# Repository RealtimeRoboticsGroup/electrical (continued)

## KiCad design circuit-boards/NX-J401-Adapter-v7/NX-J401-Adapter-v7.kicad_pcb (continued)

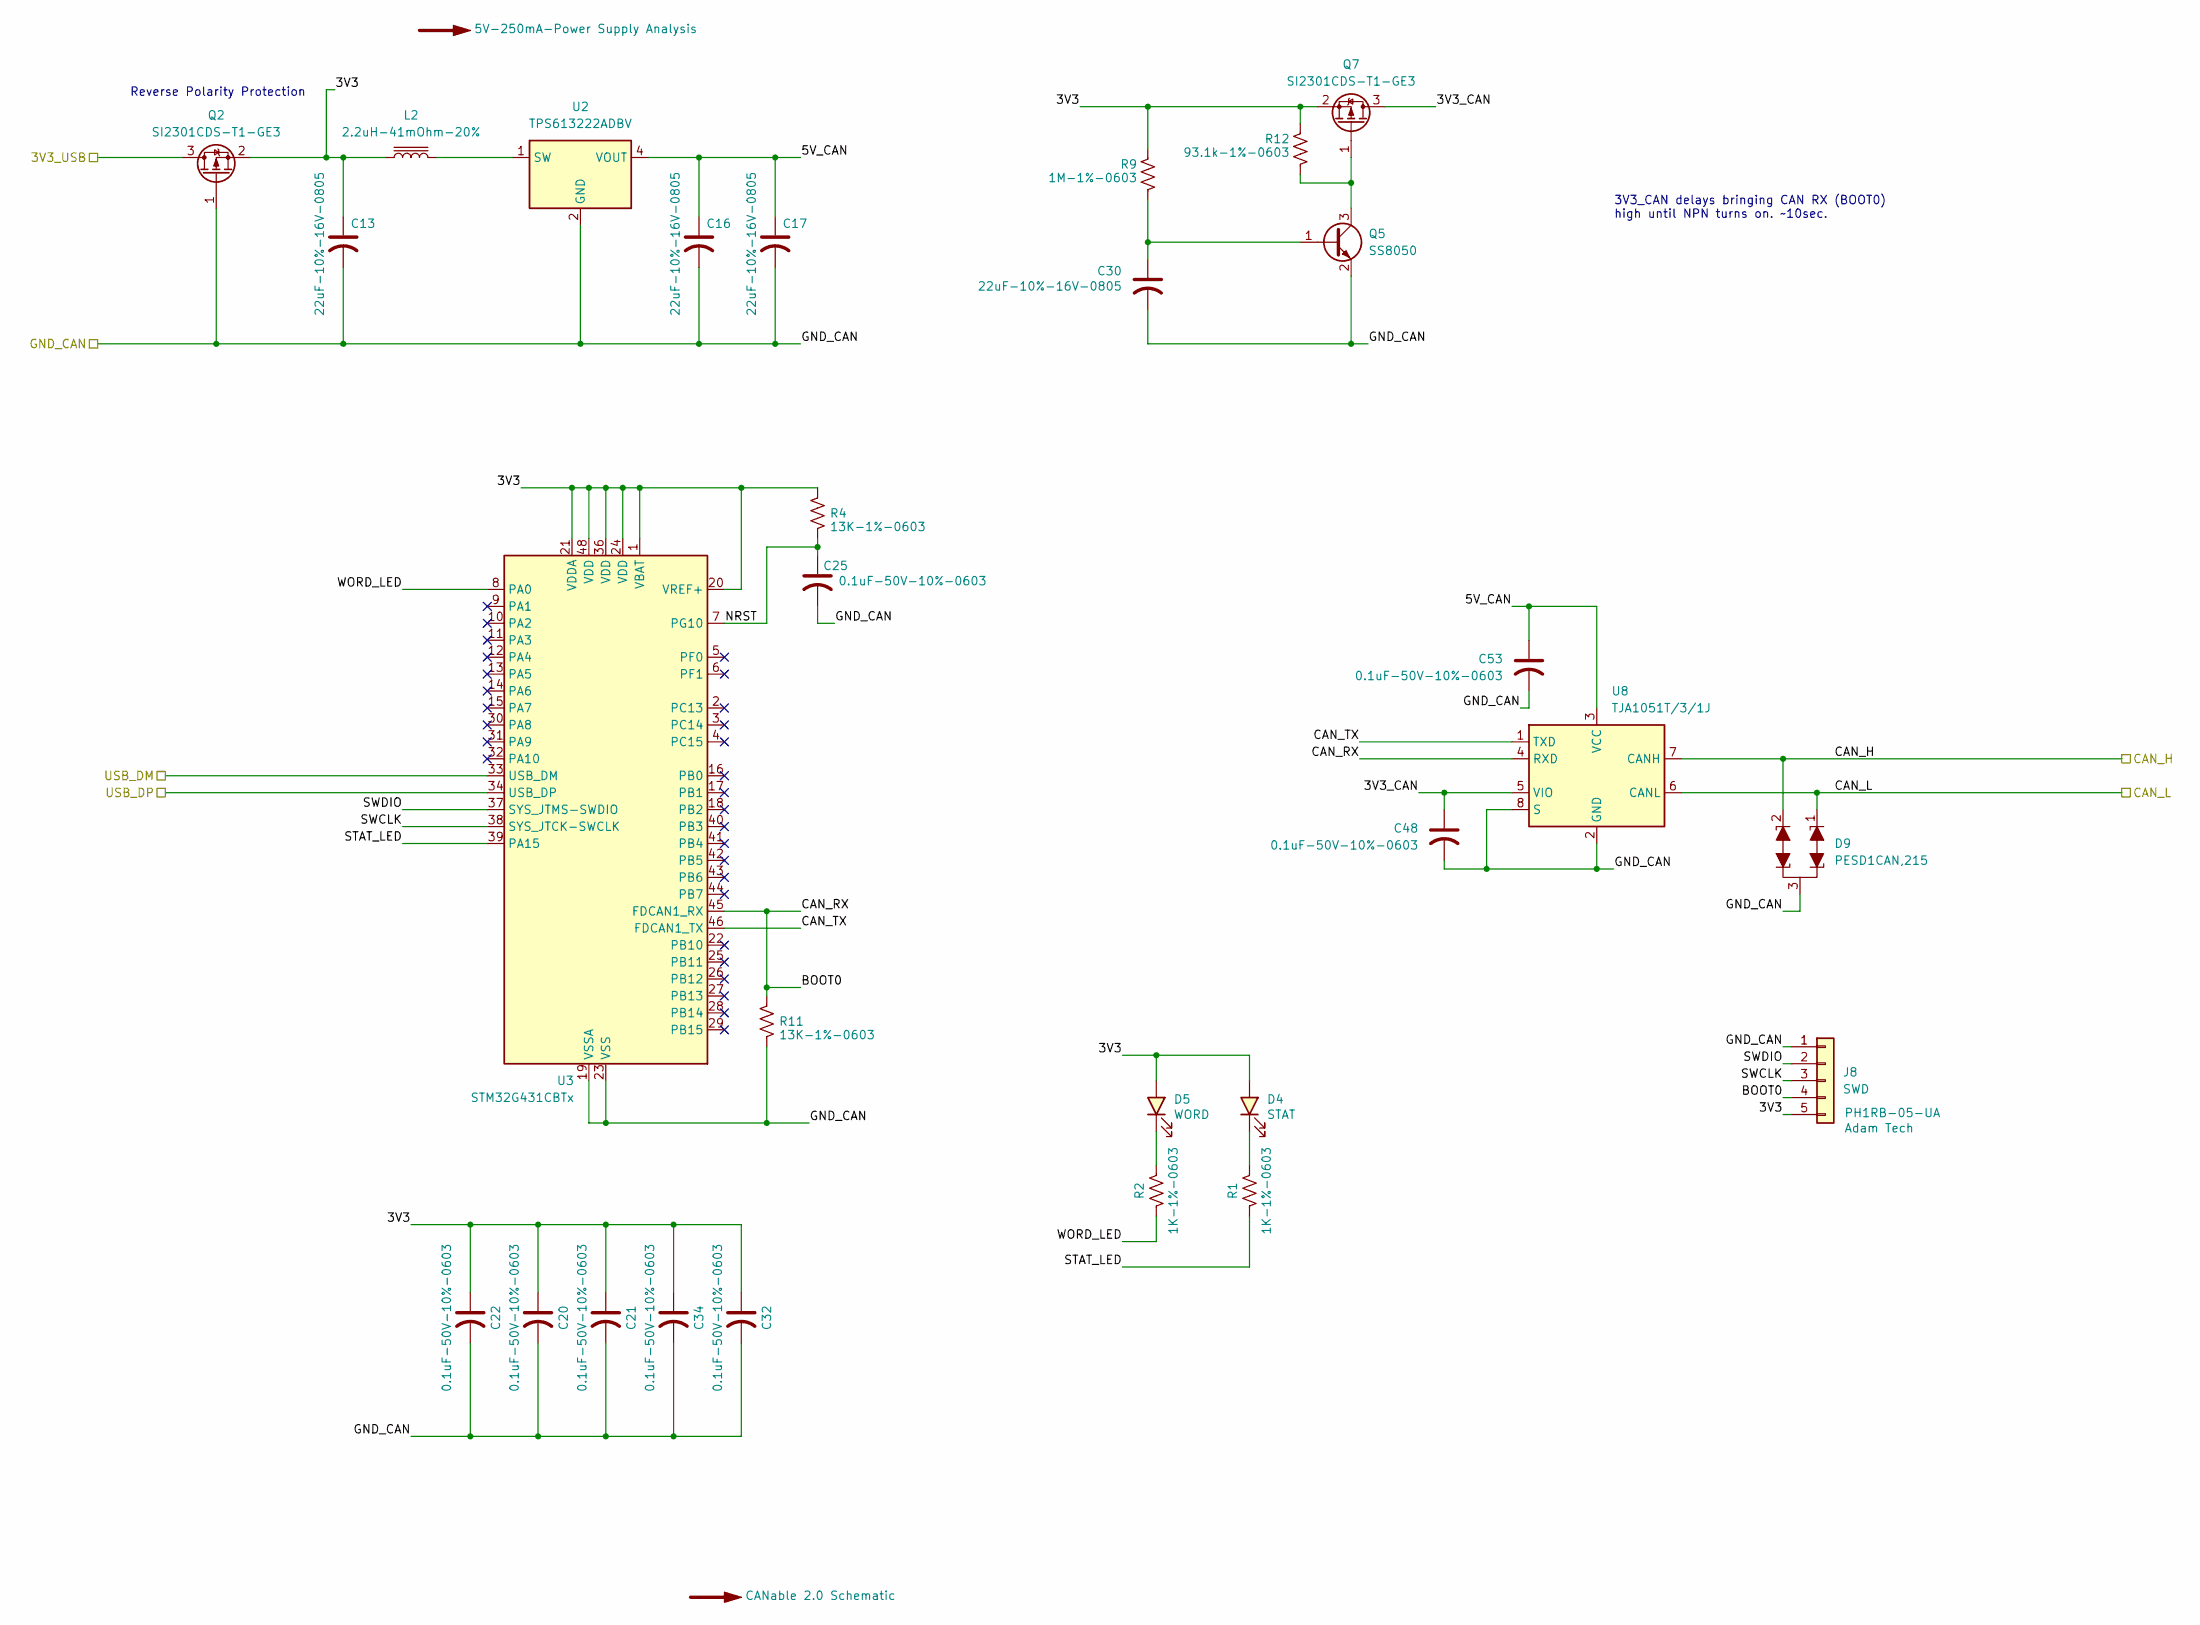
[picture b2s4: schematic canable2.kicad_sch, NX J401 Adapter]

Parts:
C13, C16, C17, C30: 22uF-10%-16V-0805; C_0805_2012Metric; MFG P/N CL21A226KOQNNNE; JLCPCB P/N C296720
C20, C21, C22, C25, C32, C34, C48, C53: 0.1uF-50V-10%-0603; C_0603_1608Metric; MFG P/N CC0603KRX7R9BB104; JLCPCB P/N C14663
D4: STAT; LED_1206_3216Metric; MFG P/N XL-3216UYC; JLCPCB P/N C965824
D5: WORD; LED_1206_3216Metric; MFG P/N XL-3216UYC; JLCPCB P/N C965824
D9: PESD1CAN; SOT-23; MFG P/N PESD1CAN,215; JLCPCB P/N C15771
J8: SWD; PinHeader_1x05_P2.54mm_Horizontal; MFG P/N PH1RB-05-UA; JLCPCB P/N XXXXXX
L2: 2.2uH-41mOhm-20%; KOHER-MDA4020-2R2M; MFG P/N MDA4020-2R2M; JLCPCB P/N C2847469
Q2, Q7: SI2301CDS-T1-GE3; SOT-23; MFG P/N SI2301CDS-T1-GE3; JLCPCB P/N C10487
Q5: SS8050; SOT-23; MFG P/N SS8050(RANGE:200-350); JLCPCB P/N C2150
R1, R2: 1K-1%-0603; R_0603_1608Metric; MFG P/N RC0603FR-071KL; JLCPCB P/N C22548
R4, R11: 13K-1%-0603; R_0603_1608Metric; MFG P/N RC0603FR-0713KL; JLCPCB P/N C137796
R9: 1M-1%-0603; R_0603_1608Metric; MFG P/N RC0603FR-071ML; JLCPCB P/N C105578
R12: 93.1k-1%-0603; R_0603_1608Metric; MFG P/N AC0603FR-0793K1L; JLCPCB P/N C228101
U2: TPS613222ADBV; SOT-23-5; MFG P/N TPS613222ADBVR; JLCPCB P/N C2071163
U3: STM32G431CBTx; LQFP-48_7x7mm_P0.5mm; MFG P/N STM32G431CBT6; JLCPCB P/N C529355
U8: TJA1051T/3/1J; SO-8_3.9x4.9mm_P1.27mm; MFG P/N TJA1051T/3/1J; JLCPCB P/N C38695

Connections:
/CANable2.0/3V3: C13.1, C20.1, C21.1, C22.1, C32.1, C34.1, D4.2 (A), D5.2 (A), J8.5, L2.1, Q2.2 (S), Q7.2 (S), R4.1, R9.1, R12.1, U3.1 (VBAT), U3.20 (VREF+), U3.21 (VDDA), U3.24 (VDD), U3.36 (VDD), U3.48 (VDD)
/CANable2.0/3V3_CAN: C48.1, Q7.3 (D), U8.5 (VIO)
/CANable2.0/3V3_USB: Q2.3 (D); also elsewhere on the board
/CANable2.0/5V_CAN: C16.1, C17.1, C53.1, U2.4 (VOUT), U8.3 (VCC)
/CANable2.0/BOOT0: J8.4, R11.1, U3.45 (FDCAN1_RX), U8.4 (RXD)
/CANable2.0/CAN_H: D9.2 (K1), U8.7 (CANH); also elsewhere on the board
/CANable2.0/CAN_L: D9.1 (K1), U8.6 (CANL); also elsewhere on the board
/CANable2.0/CAN_TX: U3.46 (FDCAN1_TX), U8.1 (TXD)
/CANable2.0/GND_CAN: C13.2, C16.2, C17.2, C20.2, C21.2, C22.2, C25.2, C30.2, C32.2, C34.2, C48.2, C53.2, D9.3 (KK), J8.1, Q2.1 (G), Q5.2 (E), R11.2, U2.2 (GND), U3.19 (VSSA), U3.23 (VSS), U3.35 (VSS), U3.47 (VSS), U8.2 (GND), U8.8 (S); also elsewhere on the board
/CANable2.0/NRST: C25.1, R4.2, U3.7 (PG10)
/CANable2.0/STAT_LED: R1.2, U3.39 (PA15)
/CANable2.0/SWCLK: J8.3, U3.38 (SYS_JTCK-SWCLK)
/CANable2.0/SWDIO: J8.2, U3.37 (SYS_JTMS-SWDIO)
/CANable2.0/USB_DM: U3.33 (USB_DM); also elsewhere on the board
/CANable2.0/USB_DP: U3.34 (USB_DP); also elsewhere on the board
/CANable2.0/WORD_LED: R2.2, U3.8 (PA0)
unnamed: D4.1 (K), R1.1
unnamed: D5.1 (K), R2.1
unnamed: C30.1, Q5.1 (B), R9.2
unnamed: Q5.3 (C), Q7.1 (G), R12.2
unnamed: L2.2, U2.1 (SW)

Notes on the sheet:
3V3_CAN delays bringing CAN RX (BOOT0) high until NPN turns on. ~10sec.
Reverse Polarity Protection

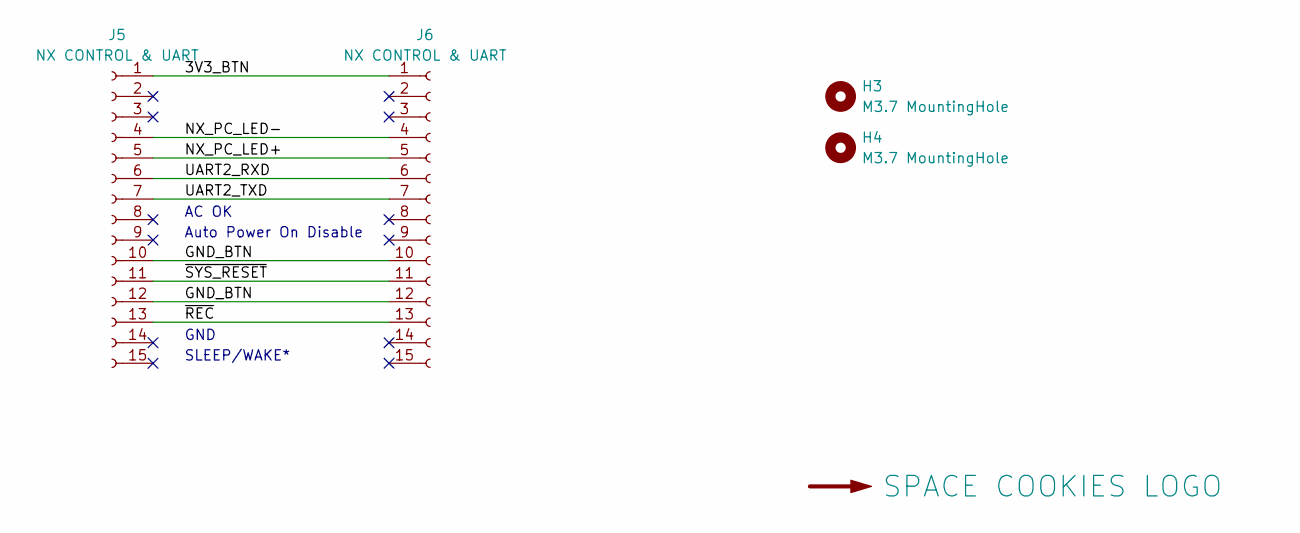
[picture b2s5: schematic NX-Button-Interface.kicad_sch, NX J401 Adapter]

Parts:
H3, H4: M3.7 MountingHole; MountingHole_3.7mm
J5, J6: NX CONTROL & UART; PinSocket_1x15_P2.54mm_Vertical; MFG P/N PPTC151LFBN-RC; JLCPCB P/N XXXXXX
LOGO2: SPACE COOKIES LOGO; SPACE_COOKIES_LOGO_7mm

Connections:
/NX-Button Interface/3V3_BTN: J5.1, J6.1
/NX-Button Interface/GND_BTN: J5.10, J5.12, J6.10, J6.12
/NX-Button Interface/NX_PC_LED+: J5.5, J6.5
/NX-Button Interface/NX_PC_LED-: J5.4, J6.4
/NX-Button Interface/UART2_RXD: J5.6, J6.6
/NX-Button Interface/UART2_TXD: J5.7, J6.7
/NX-Button Interface/~REC: J5.13, J6.13
/NX-Button Interface/~SYS_RESET: J5.11, J6.11

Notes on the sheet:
AC OK
GND
Auto Power On Disable
SLEEP/WAKE*

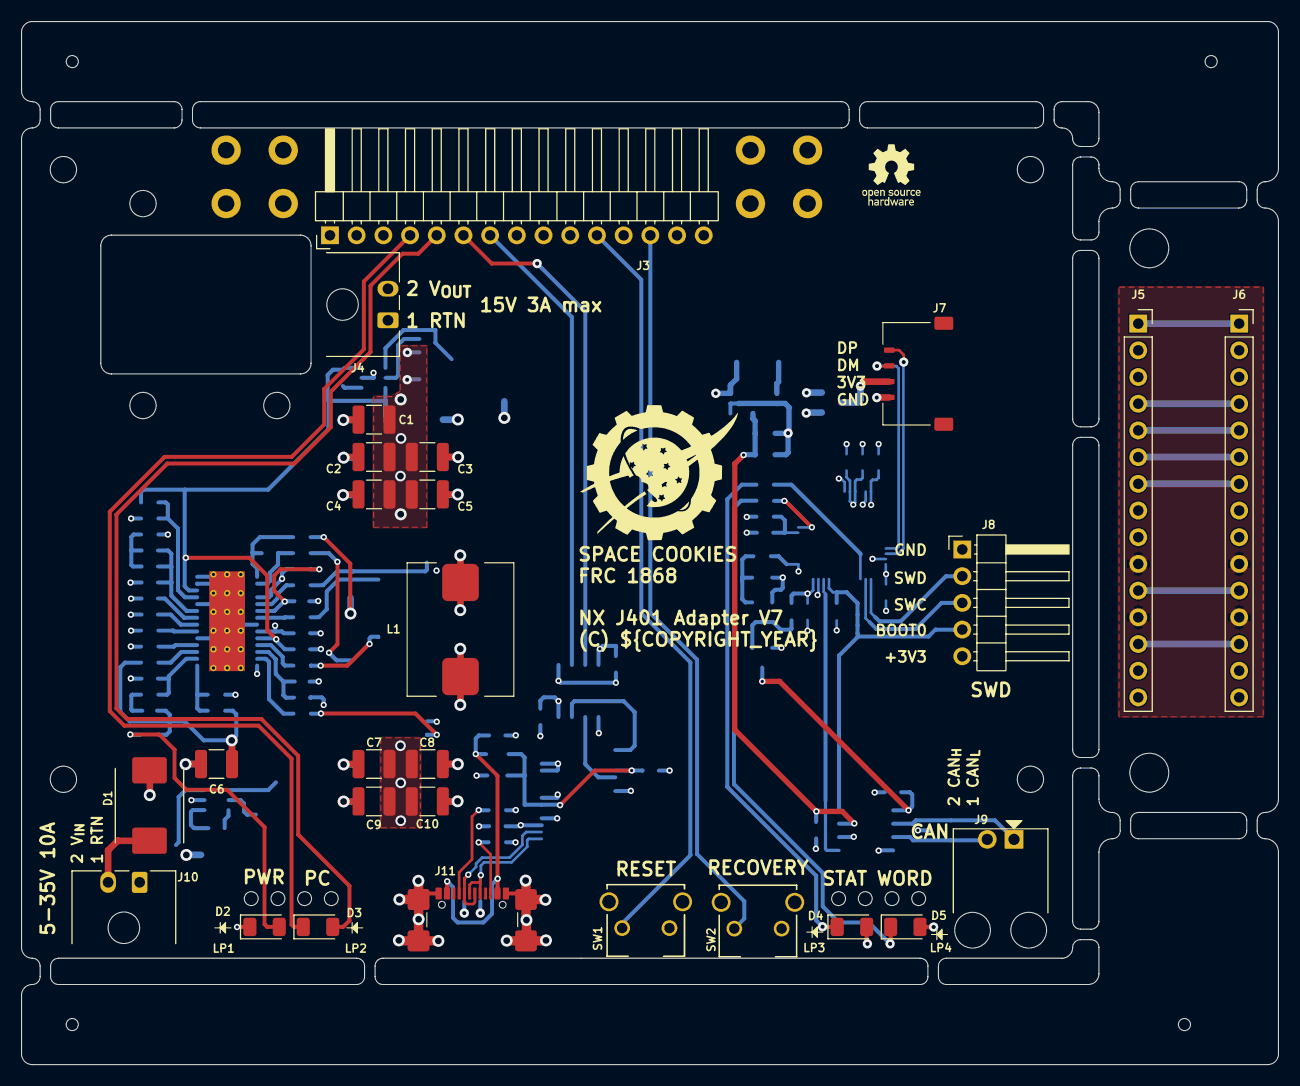
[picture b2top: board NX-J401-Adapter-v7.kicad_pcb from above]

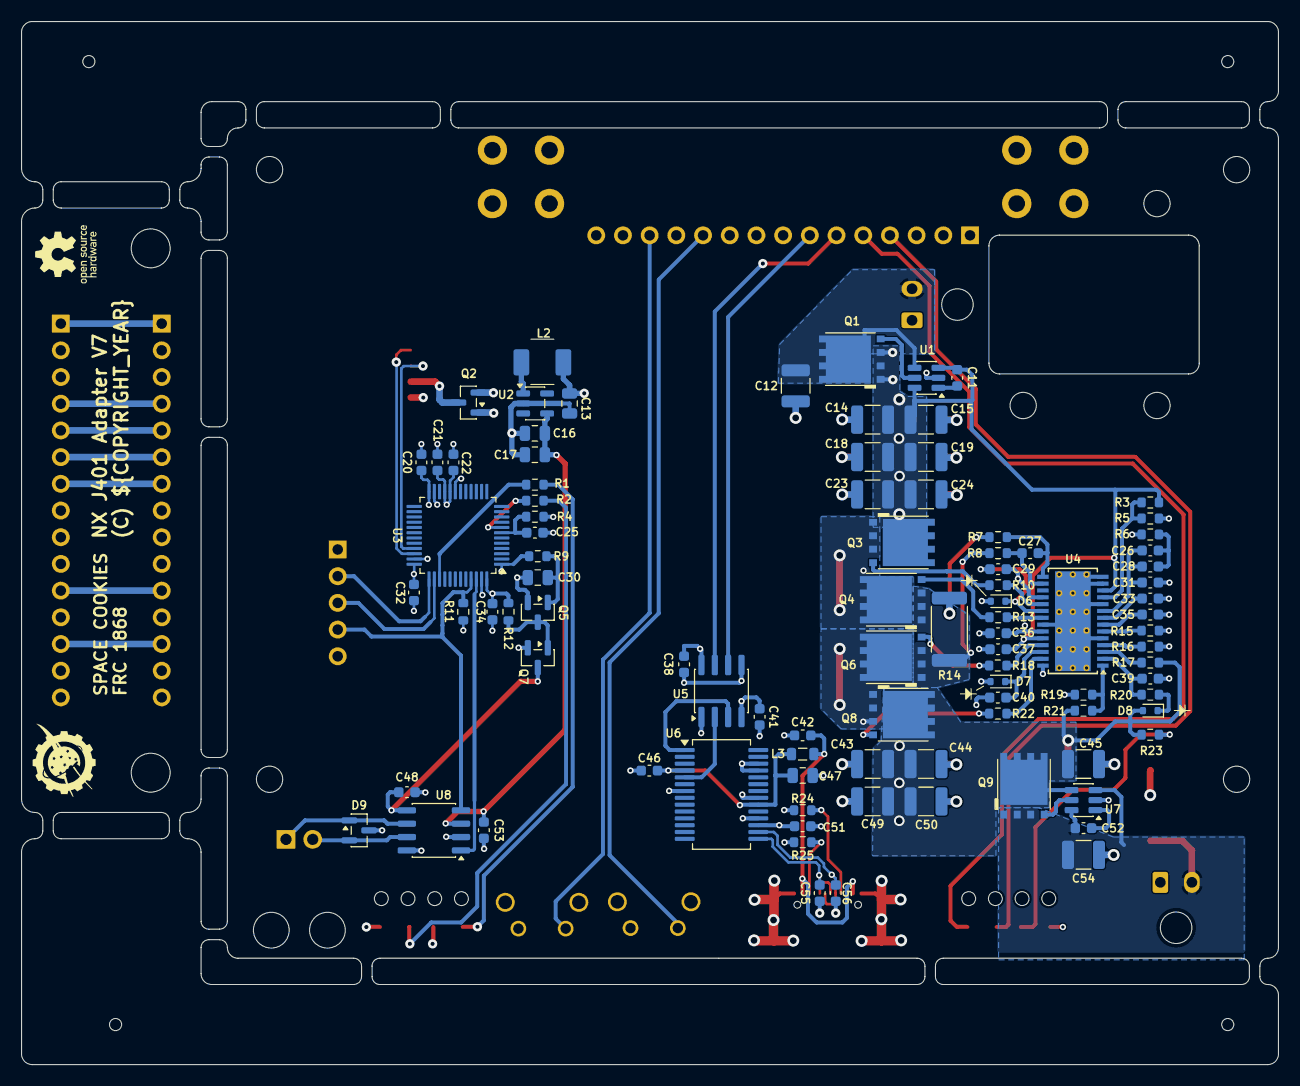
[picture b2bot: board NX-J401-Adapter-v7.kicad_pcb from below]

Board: 4 copper layers, 119.6 x 99.2 mm, 142 parts (95 on the bottom side), 84 nets.

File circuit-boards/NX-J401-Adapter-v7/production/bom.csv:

Designator,Footprint,Quantity,Value,LCSC Part #
"C1, C10, C12, C14, C15, C18, C19, C2, C23, C24, C3, C4, C43, C44, C45, C49, C5, C50, C54, C6, C7, C8, C9",1210,23,10uF-50V-10%-X7R-1210,C77102
"C11, C20, C21, C22, C25, C29, C32, C34, C37, C38, C39, C40, C41, C46, C48, C51, C52, C53",0603,18,0.1uF-50V-10%-0603,C14663
"C13, C16, C17, C30, C47",0805,5,22uF-10%-16V-0805,C296720
"C26, C28",0603,2,5.6nF-10%-50V-0603,C107095
"C27, C55, C56",0603,3,47pF-50V-10%-0603,C2168903
C31,0603,1,270pF-10%-50V-0603,C107084
"C33, C42",0603,2,15nF-10%-50V-0603,C107076
C35,0603,1,150pF-50V-10%-0603,C107075
C36,0603,1,1uF-50V-10%-0603,C105174
D1,D_SMC_Littelfuse_DO-214AB,1,24V,C284061
D2,1206,1,PWR,C5123493
D3,1206,1,PC,C5123493
D4,1206,1,STAT,C965824
D5,1206,1,WORD,C965824
"D6, D7, D8",D_SOD-523,3,BAT54KFILM,C283259
D9,SOT-23,1,PESD1CAN,C15771
"J1, J2",Keystone-7774,2,Terminal,XXXXXX
J10,Molex_Micro-Fit_3.0_43650-0200_1x02_P3.00mm_Horizontal,1,POWER,XXXXXX
J11,GCT-USB-C-USB4110-GF-A,1,USB_C_Receptacle_USB2.0_14P,C5143397
J3,PinHeader_1x15_P2.54mm_Horizontal,1,NX CONTROL & UART,XXXXXX
J4,Molex_Micro-Fit_3.0_43650-0200_1x02_P3.00mm_Horizontal,1,15V,XXXXXX
"J5, J6",PinSocket_1x15_P2.54mm_Vertical,2,NX CONTROL & UART,XXXXXX
J7,Molex-PicoLatch-5040500491,1,USB1,C177235
J8,PinHeader_1x05_P2.54mm_Horizontal,1,SWD,XXXXXX
J9,Molex-70555-0001,1,CAN1,XXXXXX
L1,Koher-MDA1050,1,2.2uH-19A-5.1mohm-20%,C2847559
L2,KOHER-MDA4020-2R2M,1,2.2uH-41mOhm-20%,C2847469
L3,0805,1,HZ0805E601R-10,C2441364
"LP1, LP2, LP3, LP4",Bivar-SLP3-150-100-F,4,Light Pipe,XXXXXX
"Q1, Q6, Q8, Q9",TI-SON5x6,4,CSD19534Q5A,C114200
"Q2, Q7",SOT-23,2,SI2301CDS-T1-GE3,C10487
"Q3, Q4",TI-SON5x6,2,CSD17578Q5A,C2871447
Q5,SOT-23,1,SS8050,C2150
"R1, R2",0603,2,1K-1%-0603,C22548
"R10, R13, R18, R22",0603,4,0R-1%-0603,C100044
"R11, R15, R4",0603,3,13K-1%-0603,C137796
"R12, R19",0603,2,93.1k-1%-0603,C228101
R14,2512,1,10mOhm-3W-1%-2512,C723413
R16,0603,1,205K-1%-0603,C22949
"R17, R23",0603,2,2K-1%-0603,C105576
R20,0603,1,10R0-1%-0603,C109318
R21,0603,1,249K-1%-0603,C706146
"R24, R25",0603,2,5.1k-1%-0603,C105580
R3,0603,1,357K-1%-0603,C227834
R5,0603,1,20K-1%-0603,C105575
R6,0603,1,5.9k-1%-0603,C23071
"R7, R8",0603,2,100R-1%-0603,C105588
R9,0603,1,1M-1%-0603,C105578
SW1,SW_TL1105VF100Q_EWI,1,RESET,XXXXXX
SW2,SW_TL1105VF100Q_EWI,1,RECOVERY,XXXXXX
"U1, U7",SOT-23-6,2,LM74700QDBVRQ1,C2941042
U2,SOT-23-5,1,TPS613222ADBV,C2071163
U3,LQFP-48_7x7mm_P0.5mm,1,STM32G431CBTx,C529355
U4,HTSSOP-28-1EP_4.4x9.7mm_P0.65mm_EP3.4x9.5mm_ThermalVias,1,LM5176PWPR,C442493
U5,SOIC-8_3.9x4.9mm_P1.27mm,1,ISO6721BDR,C5216430
U6,SSOP-28_5.3x10.2mm_P0.65mm,1,FT232RNL,C8690
U8,SO-8_3.9x4.9mm_P1.27mm,1,TJA1051T/3/1J,C38695

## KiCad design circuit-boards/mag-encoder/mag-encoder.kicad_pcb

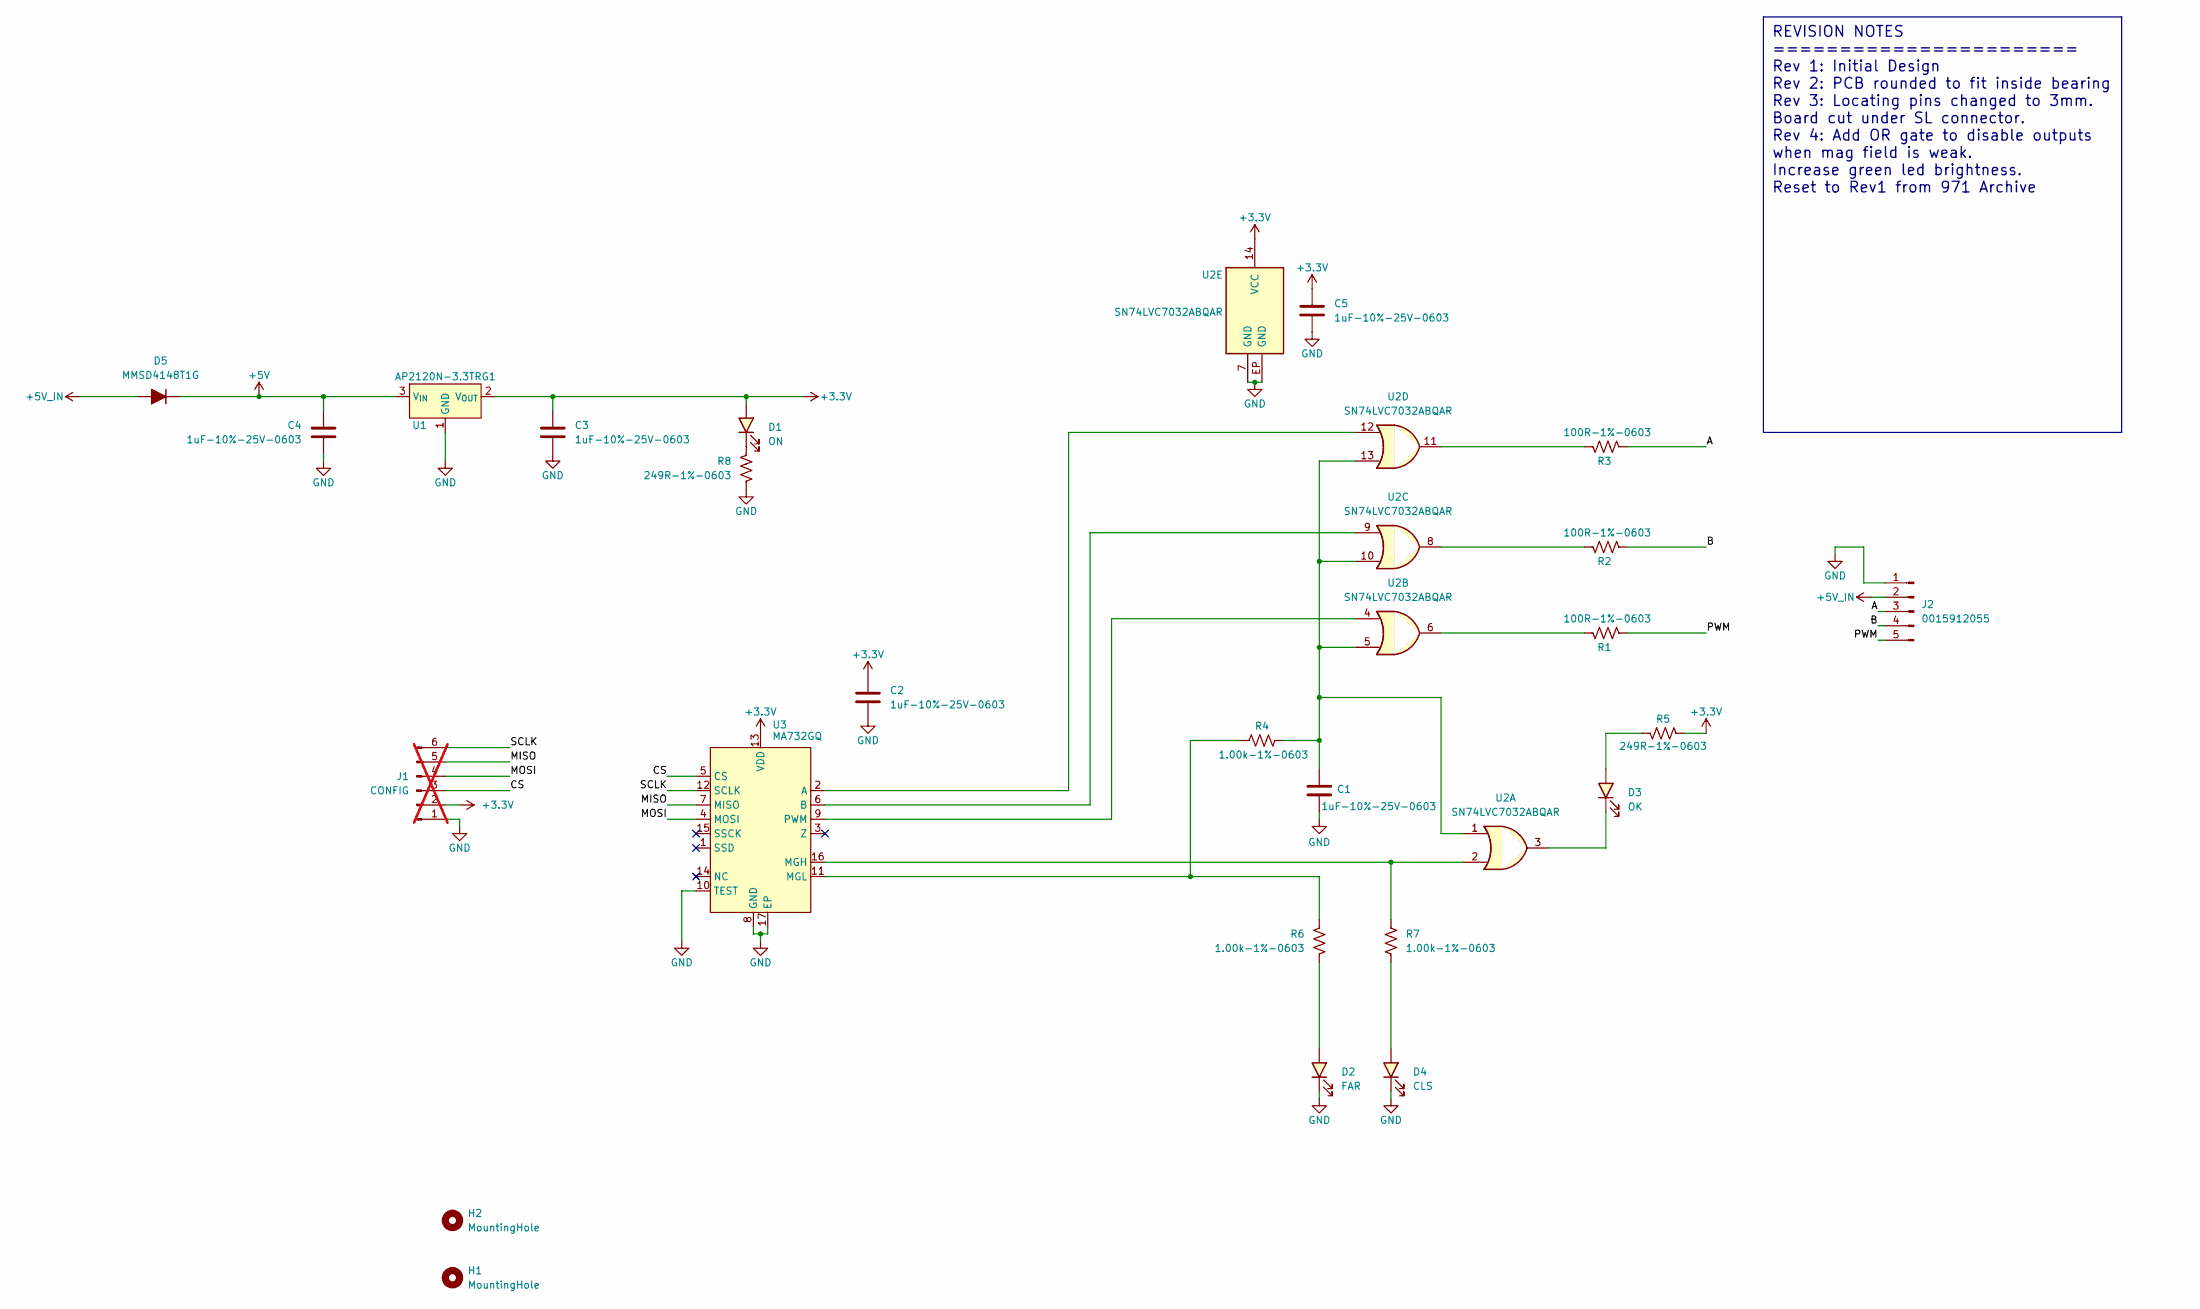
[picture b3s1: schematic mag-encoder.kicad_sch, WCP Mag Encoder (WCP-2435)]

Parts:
C1, C2, C3, C4, C5: 1uF-10%-25V-0603; C_0603_1608Metric; MFG P/N 06033C105KAT2A
D1: ON; LED_0603_1608Metric; MFG P/N 150060VS75000
D2: FAR; LED_0603_1608Metric; MFG P/N 150060RS75000
D3: OK; LED_0603_1608Metric; MFG P/N 150060VS75000
D4: CLS; LED_0603_1608Metric; MFG P/N 150060YS75000
D5: MMSD4148T1G; D_SOD-123; MFG P/N MMSD4148T1G
H1, H2: MountingHole; pin-0.100
J1: CONFIG; PinHeader_1x06_P2.54mm_Vertical; not fitted
J2: 0015912055; Molex-70634-0039; MFG P/N 0015912055
R1, R2, R3: 100R-1%-0603; R_0603_1608Metric; MFG P/N RC0603FR-07100RL
R4, R6, R7: 1.00k-1%-0603; R_0603_1608Metric; MFG P/N RC0603FR-071KL
R5, R8: 249R-1%-0603; R_0603_1608Metric; MFG P/N RC0603FR-07249RL
U1: AP2120N-3.3TRG1; SOT-23; MFG P/N AP2120N-3.3TRG1
U2: SN74LVC7032ABQAR; TI-WQFN-14-1EP_2.5x3mm_EP_1x1.5mm; MFG P/N SN74LVC7032ABQAR
U3: MA732GQ; QFN-16-1EP_3x3mm_P0.5mm_EP1.7x1.7mm; MFG P/N MA732GQ-Z

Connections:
+3.3V: C2.1, C3.1, C5.1, D1.2 (A), J1.2, R5.1, U1.2 (V_{OUT}), U2.14 (VCC), U3.13 (VDD)
+5V: C4.1, D5.1 (K), U1.3 (V_{IN})
+5V_IN: D5.2 (A), J2.2
/A: J2.3, R3.2
/B: J2.4, R2.2
/CS: J1.3, U3.5 (CS)
/MISO: J1.5, U3.7 (MISO)
/MOSI: J1.4, U3.4 (MOSI)
/PWM: J2.5, R1.2
/SCLK: J1.6, U3.12 (SCLK)
GND: C1.2, C2.2, C3.2, C4.2, C5.2, D2.1 (K), D4.1 (K), J1.1, J2.1, R8.2, U1.1 (GND), U2.7 (GND), U2.EP (GND), U3.8 (GND), U3.10 (TEST), U3.17 (EP)
unnamed: C1.1, R4.2, U2.1, U2.5, U2.10, U2.13
unnamed: D1.1 (K), R8.1
unnamed: D2.2 (A), R6.2
unnamed: D3.2 (A), R5.2
unnamed: D3.1 (K), U2.3
unnamed: D4.2 (A), R7.2
unnamed: R1.1, U2.6
unnamed: R2.1, U2.8
unnamed: R3.1, U2.11
unnamed: U2.12, U3.2 (A)
unnamed: U2.9, U3.6 (B)
unnamed: R7.1, U2.2, U3.16 (MGH)
unnamed: R4.1, R6.1, U3.11 (MGL)
unnamed: U2.4, U3.9 (PWM)

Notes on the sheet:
REVISION NOTES ======================= Rev 1: Initial Design Rev 2: PCB rounded to fit inside bearing Rev 3: Locating pins changed to 3mm. Board cut under SL connector. Rev 4: Add OR gate to disable outputs when mag field is weak. Increase green led brightness. Reset to Rev1 from 971 Archive

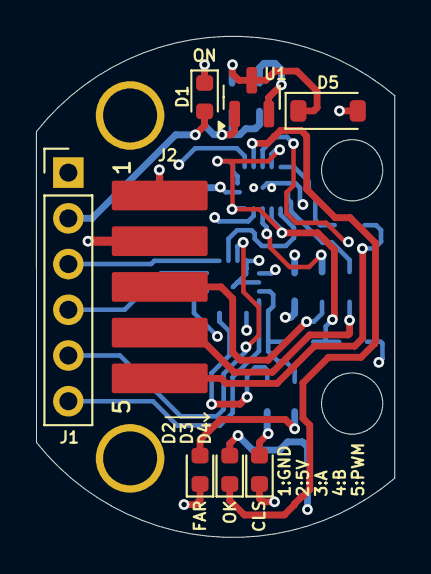
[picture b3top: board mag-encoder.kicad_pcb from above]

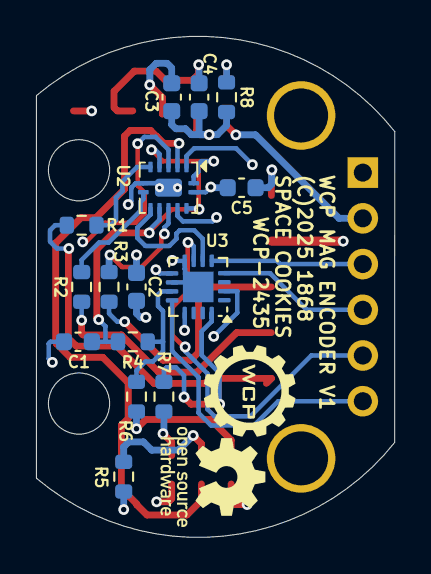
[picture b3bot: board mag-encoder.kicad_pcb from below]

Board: 4 copper layers, 19.9 x 27.8 mm, 25 parts (15 on the bottom side), 25 nets.

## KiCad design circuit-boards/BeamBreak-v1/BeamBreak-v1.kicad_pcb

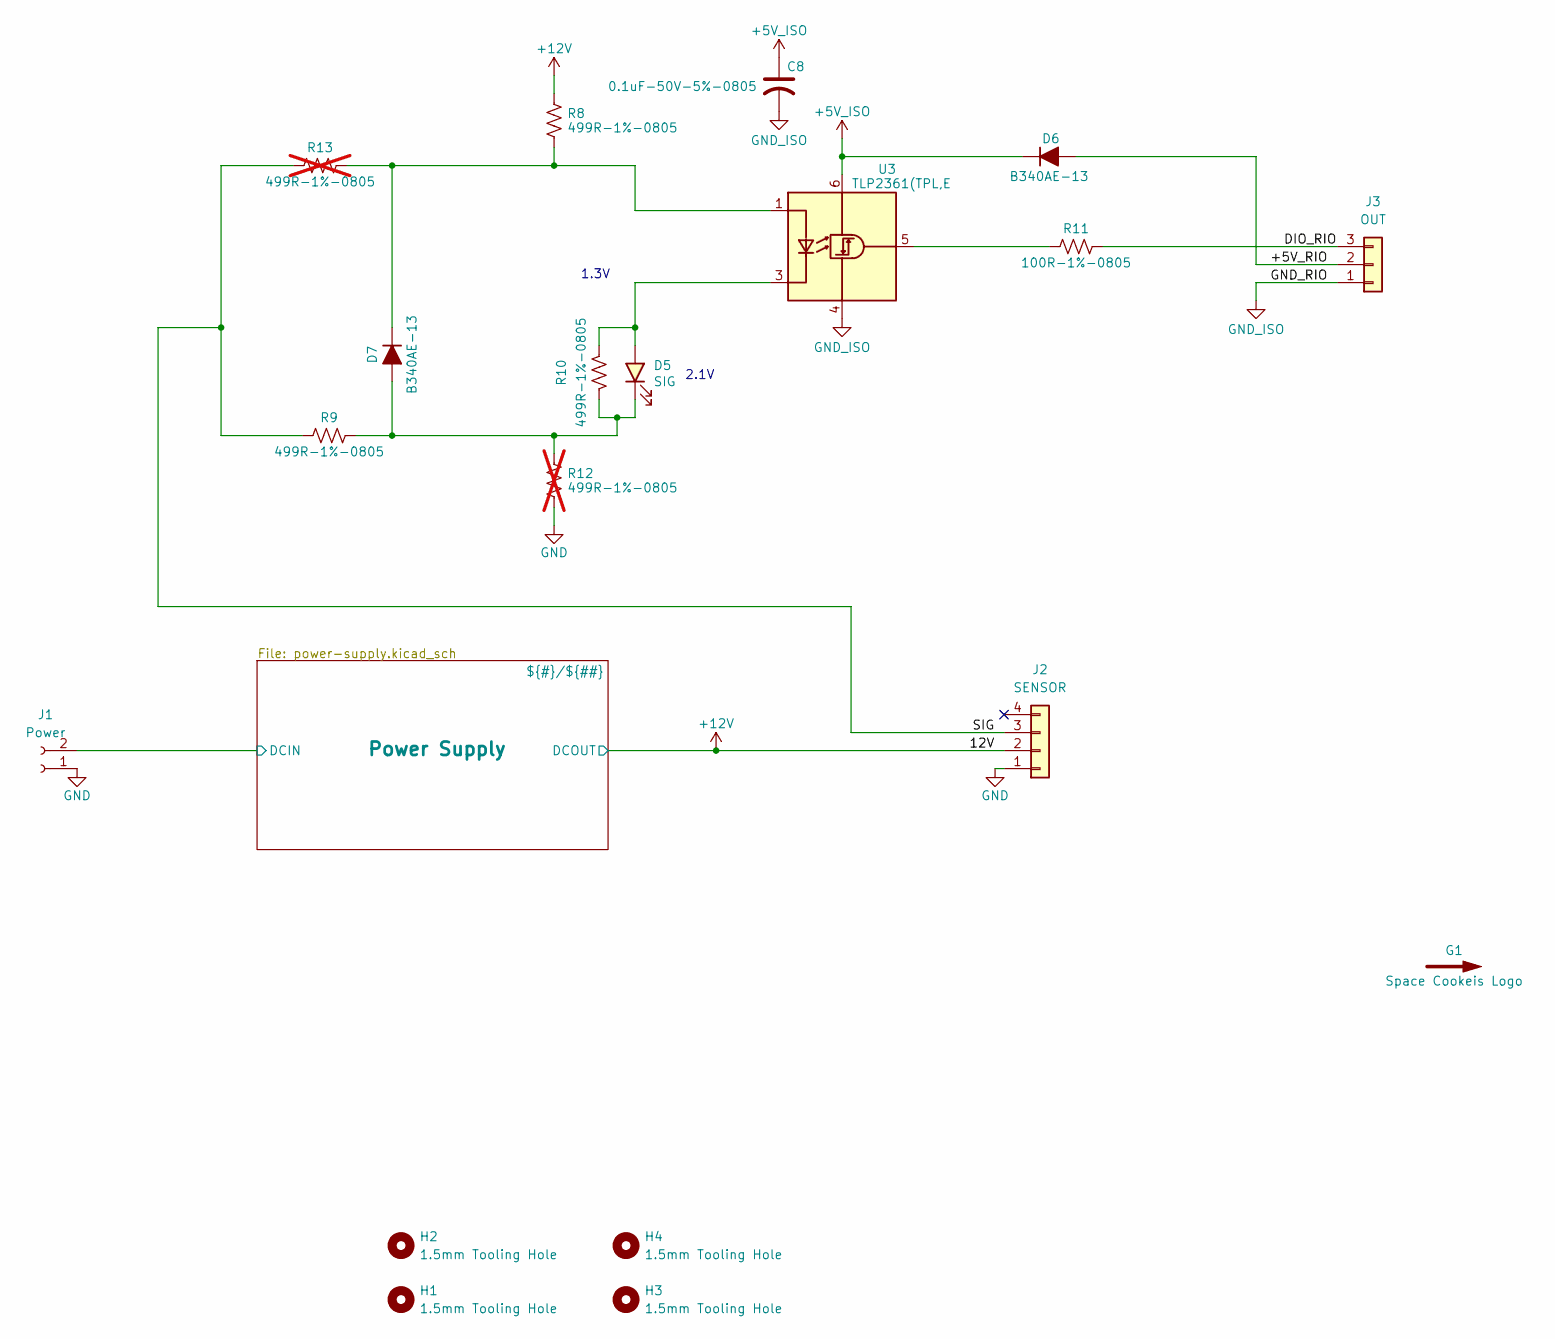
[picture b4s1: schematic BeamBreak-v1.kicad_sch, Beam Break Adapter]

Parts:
C8: 0.1uF-50V-5%-0805; C_0805_2012Metric_Pad1.18x1.45mm_HandSolder; MFG P/N C0805C104J5RACTU
D5: SIG; LED_1206_3216Metric; MFG P/N QTLP650D3TR
D6, D7: B340AE-13; D_SMA; MFG P/N B340AE-13
G1: Space Cookeis Logo; SPACE_COOKIES_LOGO_7mm
H1, H2, H3, H4: 1.5mm Tooling Hole; ToolingHole_1.5mm
J1: Power; Weidmuller-1824740000; MFG P/N 1824740000
J2: SENSOR; Molex-70555-0003; MFG P/N 70555-0038
J3: OUT; Molex-70555-0002; MFG P/N 70555-0037
R8, R9, R10: 499R-1%-0805; R_0805_2012Metric_Pad1.20x1.40mm_HandSolder; MFG P/N RC0805FR-07499RL
R11: 100R-1%-0805; R_0805_2012Metric_Pad1.20x1.40mm_HandSolder; MFG P/N CRG0805F100R
R12, R13: 499R-1%-0805; R_0805_2012Metric_Pad1.20x1.40mm_HandSolder; MFG P/N RC0805FR-07499RL; not fitted
U3: TLP2361(TPL,E; SO-5-6_4.55x3.7mm_P1.27mm; MFG P/N TLP2361(TPL,E

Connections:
+5V_ISO: C8.1, D6.1 (K), U3.6 (VDD)
+12V: J2.2, R8.2; also elsewhere on the board
/+5V_RIO: D6.2 (A), J3.2
/DIO_RIO: J3.3, R11.2
/Power Supply/DCIN: J1.2; also elsewhere on the board
/SIG: J2.3, R9.1, R13.1
GND: J1.1, J2.1, R12.1; also elsewhere on the board
GND_ISO: C8.2, J3.1, U3.4 (GND)
unnamed: D5.2 (A), R10.2, U3.3 (K)
unnamed: D5.1 (K), D7.2 (A), R9.2, R10.1, R12.2
unnamed: D7.1 (K), R8.1, R13.2, U3.1 (A)
unnamed: R11.1, U3.5 (VO)

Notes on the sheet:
2.1V
1.3V

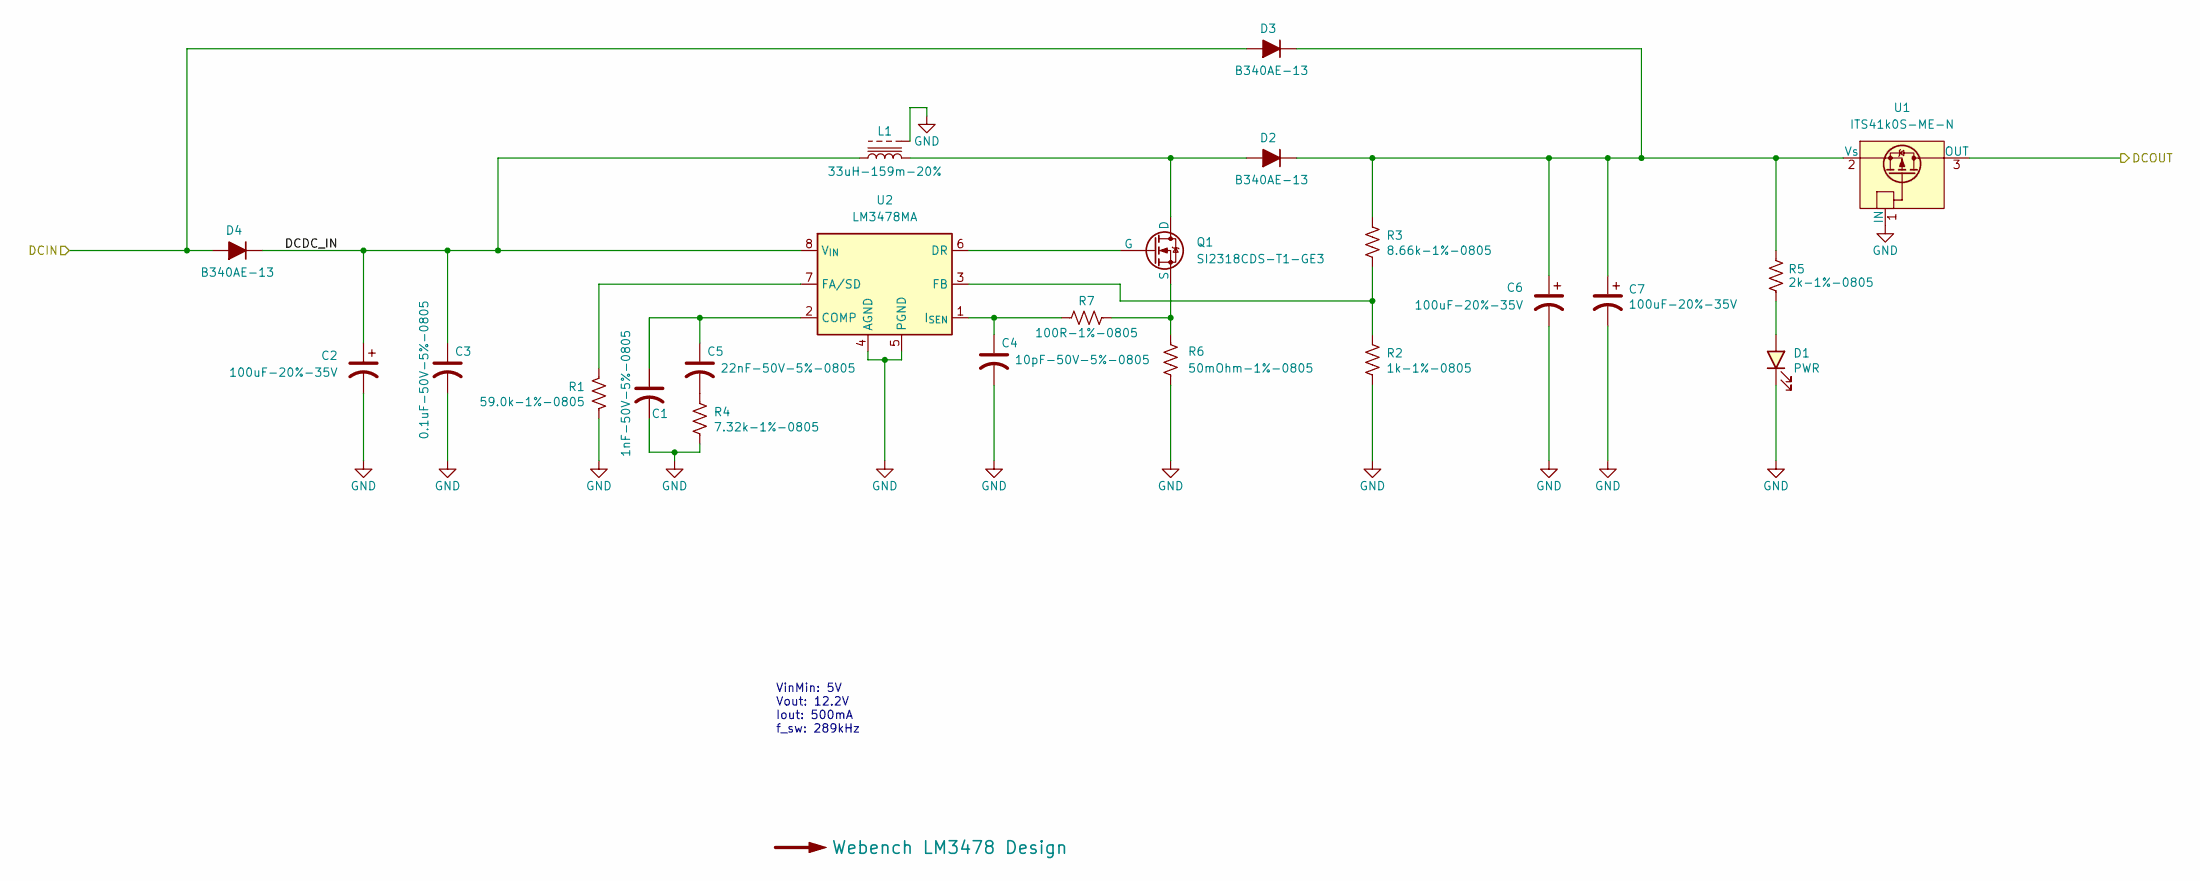
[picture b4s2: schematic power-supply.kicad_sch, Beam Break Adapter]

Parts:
C1: 1nF-50V-5%-0805; C_0805_2012Metric_Pad1.18x1.45mm_HandSolder; MFG P/N C0805C102J5GACTU
C2, C6, C7: 100uF-20%-35V; CP_Radial_D6.3mm_P2.50mm; MFG P/N RPF0608101M035K
C3: 0.1uF-50V-5%-0805; C_0805_2012Metric_Pad1.18x1.45mm_HandSolder; MFG P/N C0805C104J5RACTU
C4: 10pF-50V-5%-0805; C_0805_2012Metric_Pad1.18x1.45mm_HandSolder; MFG P/N CC0805JRNPO9BN100
C5: 22nF-50V-5%-0805; C_0805_2012Metric_Pad1.18x1.45mm_HandSolder; MFG P/N C2012C0G1H223J125AA
D1: PWR; LED_1206_3216Metric; MFG P/N QTLP650D4TR/QT15-21SYGD/S530-E2/TR8
D2, D3, D4: B340AE-13; D_SMA; MFG P/N B340AE-13
L1: 33uH-159m-20%; VishayDale-IHLE3232; MFG P/N IHLE3232DDER330M5A
Q1: SI2318CDS-T1-GE3; SOT-23-3; MFG P/N SI2318CDS-T1-GE3
R1: 59.0k-1%-0805; R_0805_2012Metric_Pad1.20x1.40mm_HandSolder; MFG P/N RC0805FR-0759KL
R2: 1k-1%-0805; R_0805_2012Metric_Pad1.20x1.40mm_HandSolder; MFG P/N RC0805FR-071KL
R3: 8.66k-1%-0805; R_0805_2012Metric_Pad1.20x1.40mm_HandSolder; MFG P/N RMCF0805FT8K66
R4: 7.32k-1%-0805; R_0805_2012Metric_Pad1.20x1.40mm_HandSolder; MFG P/N ERJ-6ENF7321V
R5: 2k-1%-0805; R_0805_2012Metric_Pad1.20x1.40mm_HandSolder; MFG P/N CRCW08052K00FKEA
R6: 50mOhm-1%-0805; R_0805_2012Metric_Pad1.20x1.40mm_HandSolder; MFG P/N ERJ-6BWFR050V
R7: 100R-1%-0805; R_0805_2012Metric_Pad1.20x1.40mm_HandSolder; MFG P/N CRG0805F100R
U1: ITS41k0S-ME-N; SOT-223-3_TabPin2; MFG P/N ITS41K0SMENHUMA1
U2: LM3478MA; SOIC-8_3.9x4.9mm_P1.27mm; MFG P/N LM3478MAX/NOPB

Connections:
+12V: U1.3 (OUT); also elsewhere on the board
/Power Supply/DCDC_IN: C2.1, C3.1, D4.1 (K), L1.1, U2.8 (V_{IN})
/Power Supply/DCIN: D3.2 (A), D4.2 (A); also elsewhere on the board
GND: C1.2, C2.2, C3.2, C4.2, C6.2, C7.2, D1.1 (K), L1.3, R1.1, R2.1, R4.1, R6.2, U1.1 (IN), U2.4 (AGND), U2.5 (PGND); also elsewhere on the board
unnamed: C5.2, R4.2
unnamed: D1.2 (A), R5.1
unnamed: D2.2 (A), L1.2, Q1.3 (D)
unnamed: C6.1, C7.1, D2.1 (K), D3.1 (K), R3.2, R5.2, U1.2 (Vs)
unnamed: Q1.1 (G), U2.6 (DR)
unnamed: Q1.2 (S), R6.1, R7.2
unnamed: C1.1, C5.1, U2.2 (COMP)
unnamed: R1.2, U2.7 (FA/SD)
unnamed: R2.2, R3.1, U2.3 (FB)
unnamed: C4.1, R7.1, U2.1 (I_{SEN})

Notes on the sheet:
VinMin: 5V Vout: 12.2V Iout: 500mA f_sw: 289kHz

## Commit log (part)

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2025-01-05 Initial commit from private repo
2025-01-14 Initial Checkin of NX J401 Adapter PCB
2025-01-14 Update NX J401 Adapter to add PC LED and swap buttons
2025-01-14 Add NX Button Interface Board
2025-01-16 Update NX-J401 and NX Button Interface boards
2025-01-16 Clarify schematic analog ground
2025-01-16 Minor fixes
2025-04-26 Add NX Indicator board. Change to one oscillator
2025-04-28 Initial checkin of WIP
2025-04-28 Changed to 1 encoder, all connectors to SMD right angle SL
2025-06-08 Add Pico CAN PCBA
2025-06-08 Minor update to PicoCAN. Add JLC assembly docs
2025-06-10 Checkin post review
2025-06-14 Changed oscillator back to ECS5032
2025-06-14 Missed schematic
2025-06-14 Update BOM
2025-06-25 Copy of https://github.com/Pier836/MCP2518FD-on-Raspberry-Pico to start picocan
2025-06-25 Set defs to match picoCAN board. Tweak code to compile
2025-09-17 Initial checkin of Button Interface and Adapter with USB-serial adapter addition
2025-09-20 Initial check in of Mini PDB V2
2025-09-20 Changed drawing sheet to Space Cookies
2025-09-20 Update using Space Cookies sheet template
2025-09-26 adjust header to match nx-adapter
2025-09-28 Add over voltage protection to NX adapter circuit. Also reduce component height
2025-10-07 Fix name on PCB
2025-10-19 Change NX-J401-Adapter to reduce the PCB standoff spacing.
2025-10-19 Update NX-ButtonInterface-v2 to be compatible with NX-J401-Adapter-v5
2025-10-19 Update step file of NX-J401-Adapter
2025-10-23 Update silk to new part number
2025-10-23 Update NX J401 to combine button interface and adapter. change header to right angle
2025-10-25 Fix bom to reduce line items. Addd zip tie slots. Add 1.5mm tooling holes
2025-11-09 Add ability to build pico2 binaries with bazel
2025-11-09 Add license
2025-11-12 Add bazel target for picocan and binary for it
2025-11-12 Fix usb printing
2025-11-25 Add ribbon cable connector and cable to schematic
2025-12-13 Adding ibom for J401 Adapter board
2025-12-18 Fixed IDC connector part number
2025-12-26 Initial check in
2025-12-26 Update footprints
2025-12-27 Pico Button Board initial placement
2025-12-28 Pico Button Board initial pcb checkin
2025-12-28 Update Pico Button Board Layout
2025-12-28 Updated Pico2 step file
2025-12-30 Changed button input circuit to use mux. Changed ADC3 to an external SPI ADC
2025-12-30 Minor schematic fix
2025-12-31 Add power over CAN to supply joystick from button interfaces.
2025-12-31 Change diodes to schottky. Change 5V setpoint to 5.18V
2025-12-31 DNP joystick pull down resistors
2026-01-01 Initial check in of roboRIO interface
2026-01-01 Update HTML bom to for DNPs
2026-01-02 Beam Break initial check in
2026-01-04 Minor schematic field update. Add jupyter notebook for power supply analysis
2026-01-05 Chagned opto-coupler to totem pole output to drive 5V DIO with weak pull-up
2026-01-05 Improved placement and routing
2026-01-06 Increased length to 2.2in
2026-01-21 Added power indicator to button board
2026-01-22 Lower impedance of battery override input
2026-01-25 initial checkin
2026-01-25 modify roborio bom to add sockets to bottom of board
2026-01-25 add bottom silk to gerbers
2026-01-25 Update power pour
2026-01-25 Changed Signal LED to Yellow
2026-02-09 Update RRIB bom to include applicable interfaces
2026-02-22 changed the roborio interface stuffing
2026-02-22 Update roborio interface assy
2026-02-22 Fix inductor mfg part number
2026-03-22 Updated repo license to Solderpad V2.1
2026-03-22 Update Apache License copyright
2026-03-22 Minor update of template to use COPYRIGHT_YEAR instead of YEAR
2026-03-23 Add open source license to mag encoder.
2026-05-18 Changed canable to use 3.3V power form USB to use key-e connector that breaks out USB and 3V3
2026-05-19 WIP update
2026-05-20 Changed USB header ot pico lock and light pipe to single row
2026-05-21 Added ideal diode circuit for reverse polarity and output or-ing
2026-05-22 Starting component placement
2026-05-22 rearrange power supply
2026-05-24 Improved placement. Pre-routing
2026-05-24 Initial fully routed PCB
2026-05-25 Initial complete routing
2026-05-26 Moved the Vout connector to increase clearance
2026-05-27 Add rails to M.2 adapter. Minor fixes to NX J401 adapter
2026-05-29 Prepare USB-m2 for manufacture
2026-06-15 Adjusted connector positioning to more closely match J401.
2026-06-20 Minor updates
